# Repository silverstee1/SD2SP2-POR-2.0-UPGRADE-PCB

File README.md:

# SD2SP2-POR-2.0-UPGRADE-PCB
Replacement 2.0 Upgrade for the lower pcb on the SD2SP2 POR MicroSD Adapter variants commonly found on amazon and aliexpress for the Gamecube Serial port 2

as long as your SD2SP2 Por version looks like the pinout in the one below this upgrade pcb will work for you as the pins must match.

SD2SP2 POR 2.0 BOM
=====================================

The PCB must be ordered in 1.2mm thickness. Surface finish must be ENIG at minimum.

**Inside PCB**

**J1:** 02x04 2.54mm Male Right Angle Pin Header - DigiKey Part# 10129382-908002BLF-ND

**U1:** OR Gate IC - Digikey Part# 1727-3067-1-ND

LCSC Part# C12488

Alt DigiKey Part# 296-1093-1-ND

LCSC Alt Part# C7470
LCSC Part# C492432

Special thanks to:
=====================================
 * citrus3000psi for the original project
 * MockyLock for the idea
 * misteraddons for the SD2SP2 PRO  
 * Extrems & emu_kidid for doing the real work needed to make this possible

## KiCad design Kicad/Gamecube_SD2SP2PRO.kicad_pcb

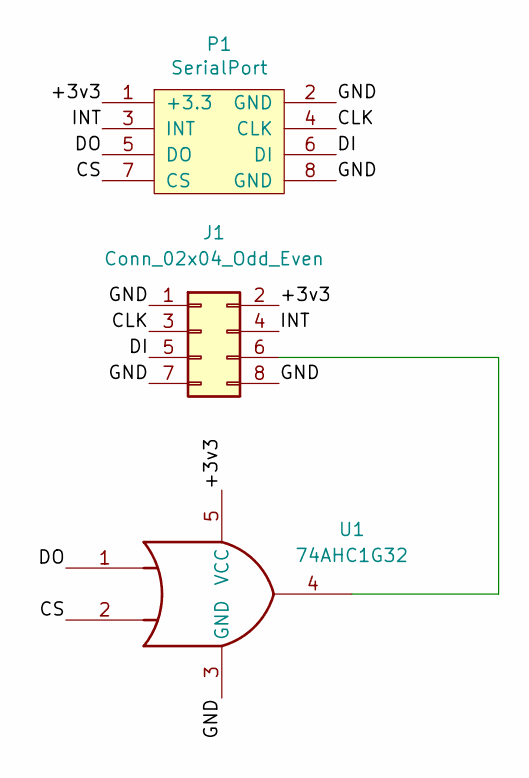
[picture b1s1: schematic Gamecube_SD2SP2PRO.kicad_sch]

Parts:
J1: Conn_02x04_Odd_Even; PinHeader_2x04_P2.54mm_Horizontal; LCSC Part C492432
P1: SerialPort; SP2_FootPrint
U1: 74AHC1G32; SC-74A-5_1.55x2.9mm_P0.95mm

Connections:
/+3v3: J1.2, P1.1 (+3.3), U1.5 (VCC)
/CLK: J1.3, P1.4 (CLK)
/CS: P1.7 (CS), U1.2
/DI: J1.5, P1.6 (DI)
/DO: P1.5 (DO), U1.1
/GND: J1.1, J1.7, J1.8, P1.2 (GND), P1.8 (GND), U1.3 (GND)
/INT: J1.4, P1.3 (INT)
unnamed: J1.6, U1.4

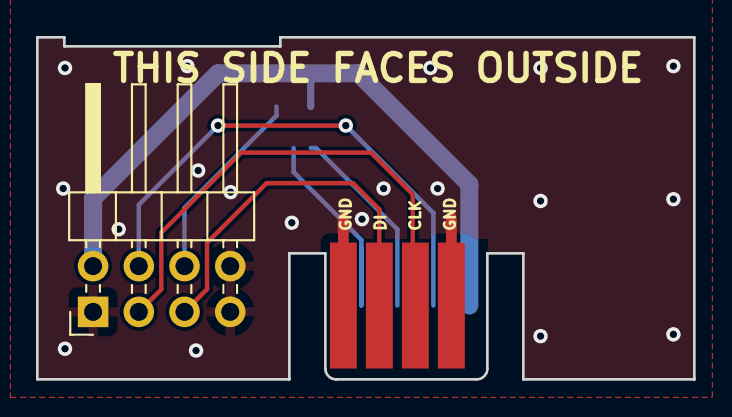
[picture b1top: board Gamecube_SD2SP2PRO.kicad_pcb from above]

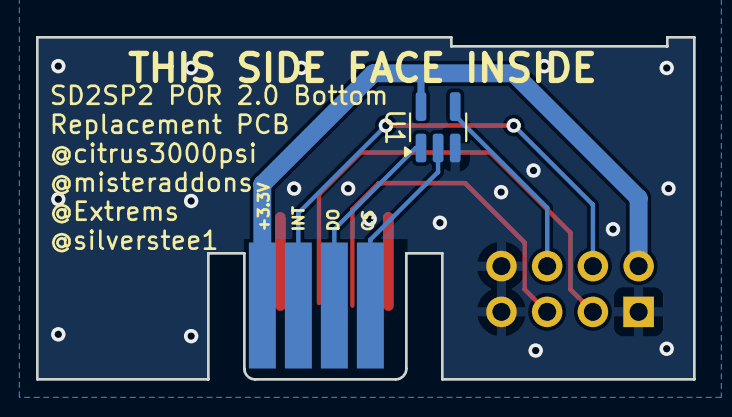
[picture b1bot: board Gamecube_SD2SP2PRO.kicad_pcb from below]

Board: 2 copper layers, 36.5 x 19.0 mm, 3 parts (2 on the bottom side), 8 nets.

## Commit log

2024-10-27 added files
    project files uploaded
2024-10-27 Create LICENSE
